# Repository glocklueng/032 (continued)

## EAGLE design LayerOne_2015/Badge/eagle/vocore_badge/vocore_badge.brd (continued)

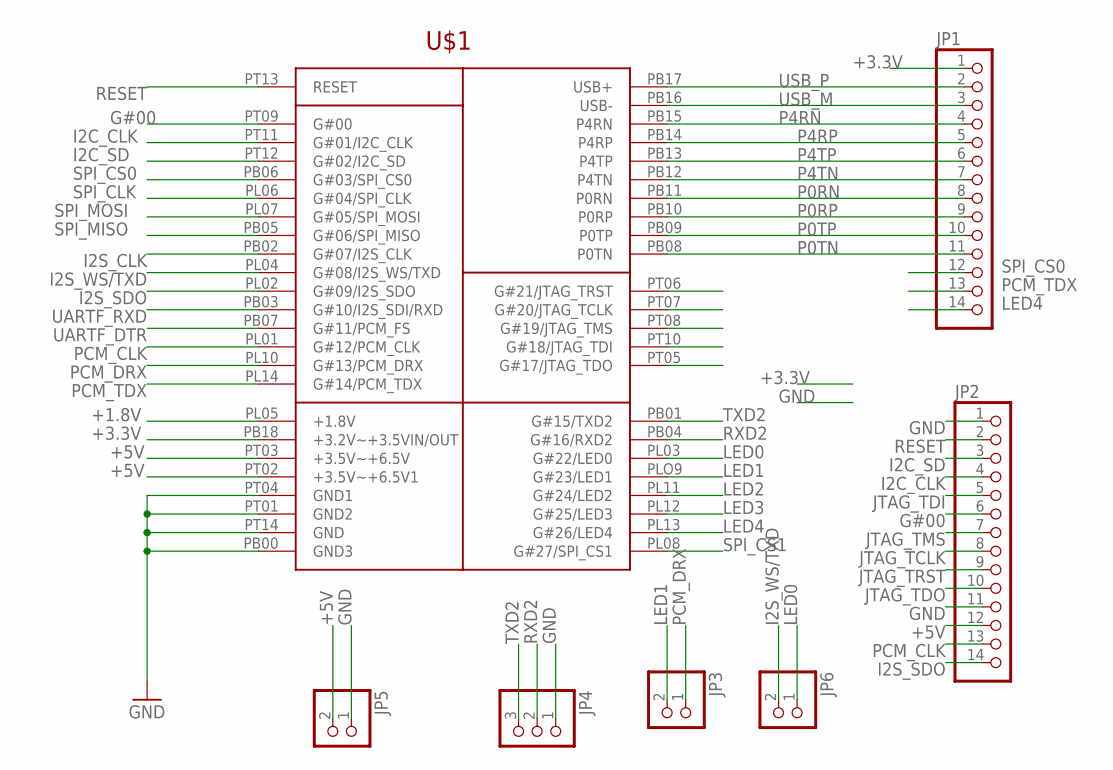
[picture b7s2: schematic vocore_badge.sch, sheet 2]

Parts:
JP1, JP2: PINHD-1X14; 1X14
JP3, JP5, JP6: PINHD-1X2; 1X02
JP4: PINHD-1X3; 1X03
U$1: VOCORE_SHIELD; VOCORE_DOC_CUSTOM

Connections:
+1.8V: U$1.PL05 (+1.8V); also elsewhere on the board
+3.3V: JP1.1, U$1.PB18 (+3.2V~+3.5VIN/OUT); also elsewhere on the board
+5V: JP2.12, JP5.2, U$1.PT02 (+3.5V~+6.5V1), U$1.PT03 (+3.5V~+6.5V); also elsewhere on the board
G#00: JP2.6, U$1.PT09 (G#00)
GND: JP2.1, JP2.11, JP4.1, JP5.1, U$1.PB00 (GND3), U$1.PT01 (GND2), U$1.PT04 (GND1), U$1.PT14 (GND); also elsewhere on the board
I2C_CLK: JP2.4, U$1.PT11 (G#01/I2C_CLK)
I2C_SD: JP2.3, U$1.PT12 (G#02/I2C_SD)
I2S_CLK: U$1.PB02 (G#07/I2S_CLK)
I2S_SDO: JP2.14, U$1.PL02 (G#09/I2S_SDO)
I2S_WS/TXD: JP6.2, U$1.PL04 (G#08/I2S_WS/TXD)
JTAG_TCLK: JP2.8, U$1.PT07 (G#20/JTAG_TCLK)
JTAG_TDI: JP2.5, U$1.PT10 (G#18/JTAG_TDI)
JTAG_TDO: JP2.10, U$1.PT05 (G#17/JTAG_TDO)
JTAG_TMS: JP2.7, U$1.PT08 (G#19/JTAG_TMS)
JTAG_TRST: JP2.9, U$1.PT06 (G#21/JTAG_TRST)
LED0: JP6.1, U$1.PL03 (G#22/LED0)
LED1: JP3.2, U$1.PLO9 (G#23/LED1)
LED2: U$1.PL11 (G#24/LED2); also elsewhere on the board
LED3: U$1.PL12 (G#25/LED3); also elsewhere on the board
LED4: JP1.14, U$1.PL13 (G#26/LED4)
P0RN: JP1.8, U$1.PB11 (P0RN); also elsewhere on the board
P0RP: JP1.9, U$1.PB10 (P0RP); also elsewhere on the board
P0TN: JP1.11, U$1.PB08 (P0TN); also elsewhere on the board
P0TP: JP1.10, U$1.PB09 (P0TP); also elsewhere on the board
P4RN: JP1.4, U$1.PB15 (P4RN); also elsewhere on the board
P4RP: JP1.5, U$1.PB14 (P4RP); also elsewhere on the board
P4TN: JP1.7, U$1.PB12 (P4TN); also elsewhere on the board
P4TP: JP1.6, U$1.PB13 (P4TP); also elsewhere on the board
PCM_CLK: JP2.13, U$1.PL01 (G#12/PCM_CLK)
PCM_DRX: JP3.1, U$1.PL10 (G#13/PCM_DRX)
PCM_TDX: JP1.13, U$1.PL14 (G#14/PCM_TDX)
RESET: JP2.2, U$1.PT13 (RESET)
RXD2: JP4.2, U$1.PB04 (G#16/RXD2); also elsewhere on the board
SPI_CLK: U$1.PL06 (G#04/SPI_CLK); also elsewhere on the board
SPI_CS0: JP1.12, U$1.PB06 (G#03/SPI_CS0)
SPI_CS1: U$1.PL08 (G#27/SPI_CS1); also elsewhere on the board
SPI_MISO: U$1.PB05 (G#06/SPI_MISO); also elsewhere on the board
SPI_MOSI: U$1.PL07 (G#05/SPI_MOSI); also elsewhere on the board
TXD2: JP4.3, U$1.PB01 (G#15/TXD2); also elsewhere on the board
UARTF_DTR: U$1.PB07 (G#11/PCM_FS); also elsewhere on the board
UARTF_RXD: U$1.PB03 (G#10/I2S_SDI/RXD); also elsewhere on the board
USB_M: JP1.3, U$1.PB16 (USB-); also elsewhere on the board
USB_P: JP1.2, U$1.PB17 (USB+); also elsewhere on the board

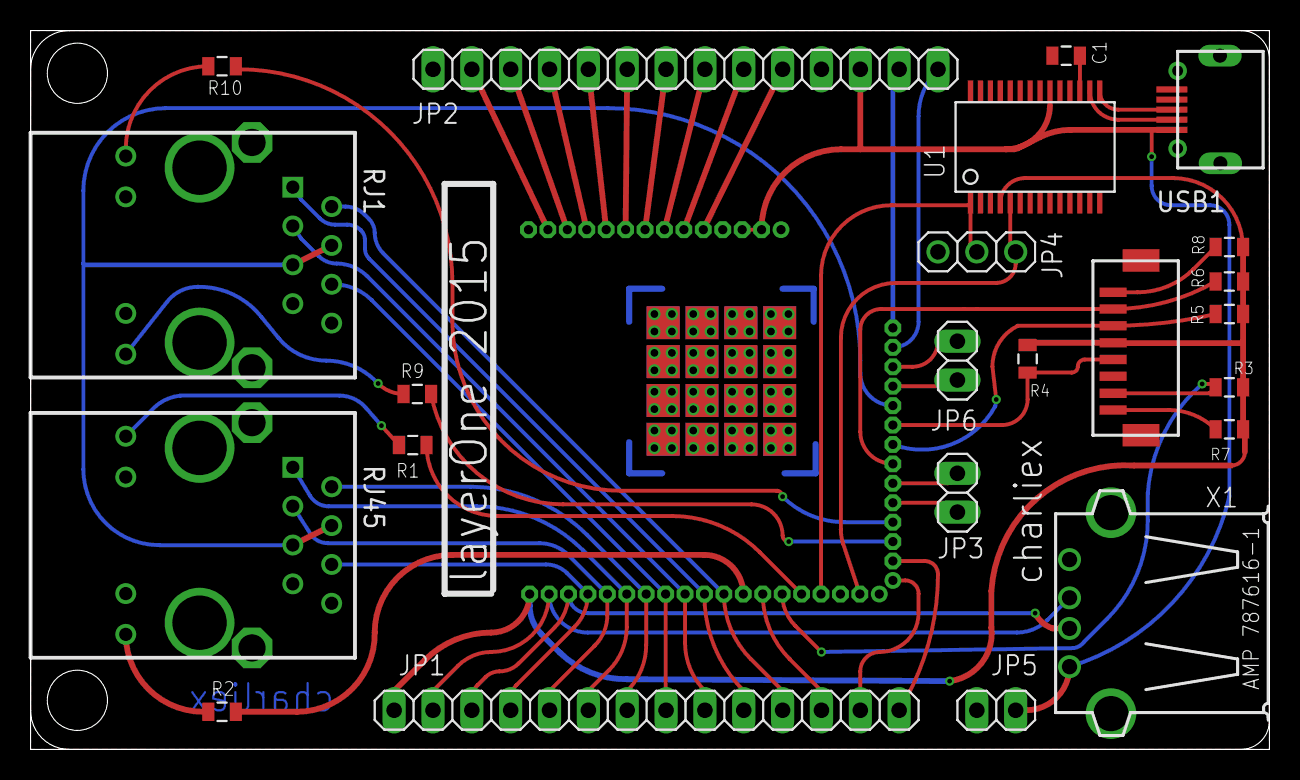
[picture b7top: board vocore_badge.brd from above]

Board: 2 copper layers, 81.0 x 47.0 mm, 24 parts (1 on the bottom side), 51 nets.

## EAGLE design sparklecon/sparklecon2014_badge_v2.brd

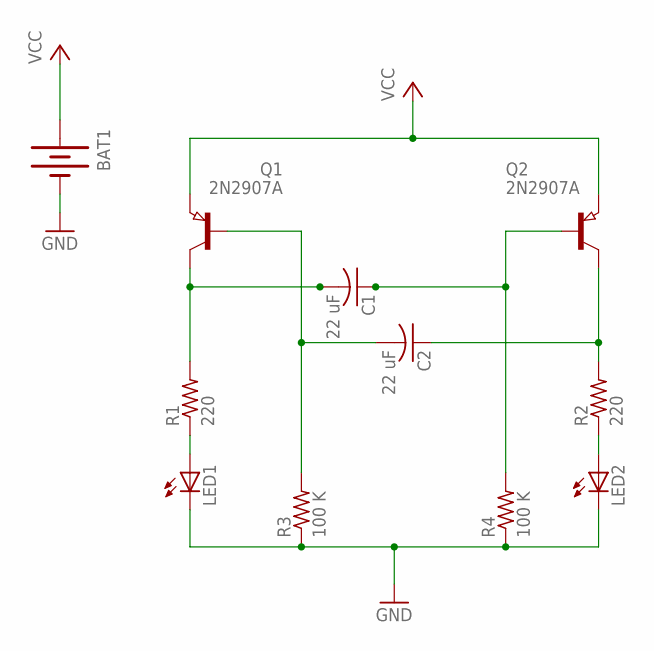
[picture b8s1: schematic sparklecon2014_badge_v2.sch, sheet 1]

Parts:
BAT1: BATTERY20PTH; BATTCOM_20MM_PTH
C1, C2: 22 uF; C1206K
LED1, LED2: LEDCHIPLED_1206; CHIPLED_1206
Q1, Q2: 2N2907A; SOT23
R1, R2: 220; R0805
R3, R4: 100 K; R0805

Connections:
GND: BAT1.2 (-), LED1.C, LED2.C, R3.1, R4.1; also elsewhere on the board
unnamed: C1.2, Q1.3 (C), R1.2
unnamed: C2.2, Q1.1 (B), R3.2
unnamed: LED2.A, R2.1
unnamed: LED1.A, R1.1
unnamed: C2.1, Q2.3 (C), R2.2
unnamed: C1.1, Q2.1 (B), R4.2
VCC: BAT1.1 (+), Q1.2 (E), Q2.2 (E)

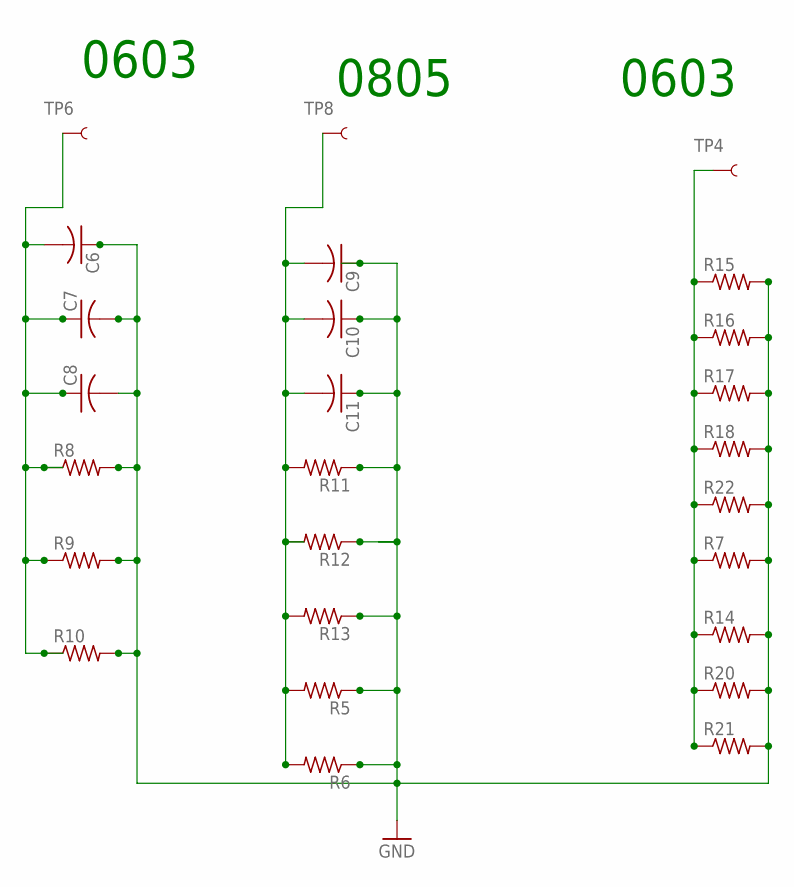
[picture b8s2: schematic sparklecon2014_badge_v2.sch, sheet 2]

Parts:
C6, C7, C8: C-USC1206; C1206
C9, C10, C11: C-USC0805; C0805
R5, R6, R11, R12, R13: R-US_R0805; R0805
R7, R14, R20, R21, R22: R-US_R0402; R0402
R8, R9, R10: R-US_R1206; R1206
R15, R16, R17, R18: R-US_R0603; R0603
TP4, TP6, TP8: TEST-POINT3X5; PAD.03X.05

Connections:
GND: C6.1, C7.2, C8.2, C9.1, C10.1, C11.1, R5.1, R6.1, R7.2, R8.2, R9.2, R10.2, R11.1, R12.1, R13.1, R14.2, R15.2, R16.2, R17.2, R18.2, R20.2, R21.2, R22.2; also elsewhere on the board
unnamed: R7.1, R14.1, R15.1, R16.1, R17.1, R18.1, R20.1, R21.1, R22.1, TP4.P$1
unnamed: C6.2, C7.1, C8.1, R8.1, R9.1, R10.1, TP6.P$1
unnamed: C9.2, C10.2, C11.2, R5.2, R6.2, R11.2, R12.2, R13.2, TP8.P$1

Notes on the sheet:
0603
0805

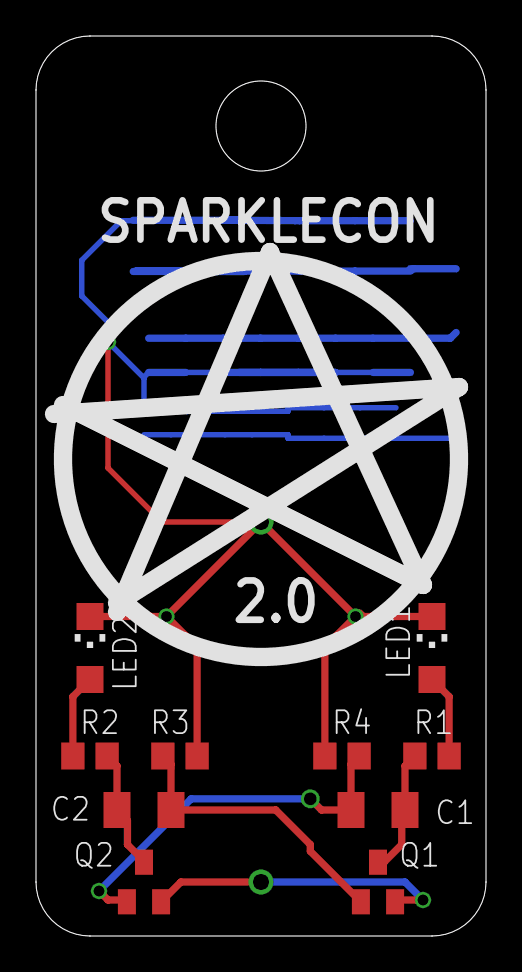
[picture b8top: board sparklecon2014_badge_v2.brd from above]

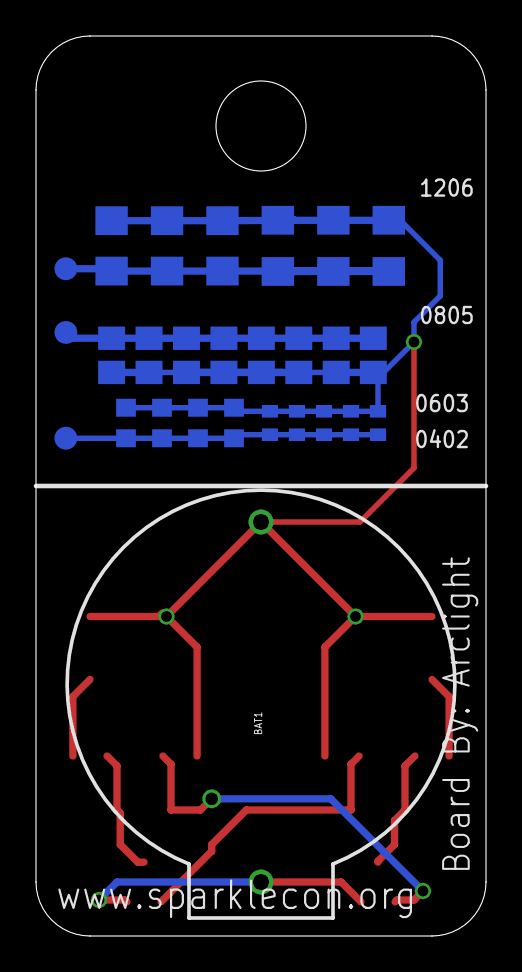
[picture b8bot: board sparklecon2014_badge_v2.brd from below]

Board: 2 copper layers, 25.0 x 50.0 mm, 37 parts (27 on the bottom side), 11 nets.

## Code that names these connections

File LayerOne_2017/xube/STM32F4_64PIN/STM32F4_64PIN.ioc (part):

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Mcu.Name=STM32F446R(C-E)Tx
Mcu.Package=LQFP64
Mcu.UserName=STM32F446RETx
PA10.GPIOParameters=GPIO_Label
PA10.GPIO_Label=USB_ID
PA10.Mode=OTG/Dual_Role_Device
PA10.Signal=USB_OTG_FS_ID
PA11.GPIOParameters=GPIO_Label
PA11.GPIO_Label=D-
PA11.Mode=OTG/Dual_Role_Device
PA11.Signal=USB_OTG_FS_DM
PA12.GPIOParameters=GPIO_Label
PA12.GPIO_Label=D+
PA12.Mode=OTG/Dual_Role_Device
PA12.Signal=USB_OTG_FS_DP
PA13.Mode=Serial_Wire
PA13.Signal=SYS_JTMS-SWDIO
PA14.Mode=Serial_Wire
PA14.Signal=SYS_JTCK-SWCLK
PA2.GPIOParameters=GPIO_Label
PA2.GPIO_Label=TFT_RESET
PA2.Signal=GPIO_Output
PA4.Signal=COMP_DAC1_group
PA5.GPIOParameters=GPIO_Label
PA5.GPIO_Label=TFT_SCK
PA5.Mode=Full_Duplex_Slave
PA5.Signal=SPI1_SCK
PA6.GPIOParameters=GPIO_Label
PA6.GPIO_Label=TFT_MISO
PA6.Mode=Full_Duplex_Slave
PA6.Signal=SPI1_MISO
PA7.GPIOParameters=GPIO_Label
PA7.GPIO_Label=TFT_MOSI
PA7.Mode=Full_Duplex_Slave
PA7.Signal=SPI1_MOSI
PA8.GPIOParameters=GPIO_Label
PA8.GPIO_Label=TFT_DC
PA8.Signal=GPIO_Output
PA9.Mode=Activate_VBUS
PA9.Signal=USB_OTG_FS_VBUS
PB10.GPIOParameters=GPIO_Label
PB10.GPIO_Label=SD_SCK
PB10.Mode=Full_Duplex_Master
PB10.Signal=SPI2_SCK
PB12.Mode=OTG/Dual-Role-Device-FS
PB12.Signal=USB_OTG_HS_ID
PB13.Mode=Activate_VBUS_FS
PB13.Signal=USB_OTG_HS_VBUS
PB14.Mode=OTG/Dual-Role-Device-FS
PB14.Signal=USB_OTG_HS_DM
PB15.Mode=OTG/Dual-Role-Device-FS
PB15.Signal=USB_OTG_HS_DP
PB5.Mode=Slave
PB5.Signal=CAN2_RX
PB6.Mode=Slave
PB6.Signal=CAN2_TX
PB8.Mode=Master
PB8.Signal=CAN1_RX
PB9.Mode=Master
PB9.Signal=CAN1_TX
PC1.GPIOParameters=GPIO_Label
PC1.GPIO_Label=SD_MOSI
PC1.Mode=Full_Duplex_Master
PC1.Signal=SPI2_MOSI
PC2.GPIOParameters=GPIO_Label
PC2.GPIO_Label=SD_MISO
PC2.Mode=Full_Duplex_Master
PC2.Signal=SPI2_MISO
PC7.GPIOParameters=GPIO_Label
PC7.GPIO_Label=TFT_CS
PC7.Signal=GPIO_Output
PC9.GPIOParameters=GPIO_Label
PC9.GPIO_Label=TFT_LCD
PC9.Signal=GPIO_Output
PH0-OSC_IN.Mode=HSE-External-Oscillator
PH0-OSC_IN.Signal=RCC_OSC_IN
PH1-OSC_OUT.Mode=HSE-External-Oscillator
PH1-OSC_OUT.Signal=RCC_OSC_OUT
RCC.SYSCLKFreq_VALUE=120000000
RCC.SYSCLKSource=RCC_SYSCLKSOURCE_PLLCLK
board=STM32F4_64PIN

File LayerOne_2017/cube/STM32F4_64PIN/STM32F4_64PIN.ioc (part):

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Mcu.Name=STM32F446R(C-E)Tx
Mcu.Package=LQFP64
Mcu.UserName=STM32F446RETx
PA11.GPIOParameters=GPIO_Speed,GPIO_PuPd,GPIO_Mode
PA11.GPIO_Mode=GPIO_MODE_AF_PP
PA11.GPIO_PuPd=GPIO_NOPULL
PA11.GPIO_Speed=GPIO_SPEED_FREQ_VERY_HIGH
PA11.Mode=Host_Only
PA11.Signal=USB_OTG_FS_DM
PA12.GPIOParameters=GPIO_Speed,GPIO_PuPd,GPIO_Mode
PA12.GPIO_Mode=GPIO_MODE_AF_PP
PA12.GPIO_PuPd=GPIO_NOPULL
PA12.GPIO_Speed=GPIO_SPEED_FREQ_VERY_HIGH
PA12.Mode=Host_Only
PA12.Signal=USB_OTG_FS_DP
PA13.Mode=Serial_Wire
PA13.Signal=SYS_JTMS-SWDIO
PA14.Mode=Serial_Wire
PA14.Signal=SYS_JTCK-SWCLK
PA4.Signal=COMP_DAC1_group
PA5.GPIOParameters=GPIO_Speed,GPIO_PuPd,GPIO_Mode
PA5.GPIO_Mode=GPIO_MODE_AF_PP
PA5.GPIO_PuPd=GPIO_NOPULL
PA5.GPIO_Speed=GPIO_SPEED_FREQ_VERY_HIGH
PA5.Mode=Full_Duplex_Slave
PA5.Signal=SPI1_SCK
PA6.GPIOParameters=GPIO_Speed,GPIO_PuPd,GPIO_Mode
PA6.GPIO_Mode=GPIO_MODE_AF_PP
PA6.GPIO_PuPd=GPIO_NOPULL
PA6.GPIO_Speed=GPIO_SPEED_FREQ_VERY_HIGH
PA6.Mode=Full_Duplex_Slave
PA6.Signal=SPI1_MISO
PA7.GPIOParameters=GPIO_Speed,GPIO_PuPd,GPIO_Mode
PA7.GPIO_Mode=GPIO_MODE_AF_PP
PA7.GPIO_PuPd=GPIO_NOPULL
PA7.GPIO_Speed=GPIO_SPEED_FREQ_VERY_HIGH
PA7.Mode=Full_Duplex_Slave
PA7.Signal=SPI1_MOSI
PA8.GPIOParameters=GPIO_Speed,PinState,GPIO_PuPd,GPIO_ModeDefaultOutputPP
PA8.GPIO_ModeDefaultOutputPP=GPIO_MODE_OUTPUT_PP
PA8.GPIO_PuPd=GPIO_NOPULL
PA8.GPIO_Speed=GPIO_SPEED_FREQ_LOW
PA8.PinState=GPIO_PIN_RESET
PA8.Signal=GPIO_Output
PA9.Mode=Activate_VBUS
PA9.Signal=USB_OTG_FS_VBUS
PB0.GPIOParameters=GPIO_PuPd,GPIO_Mode
PB0.GPIO_Mode=GPIO_MODE_INPUT
PB0.GPIO_PuPd=GPIO_NOPULL
PB0.Signal=GPIO_Input
PB1.GPIOParameters=GPIO_PuPd,GPIO_Mode
PB1.GPIO_Mode=GPIO_MODE_INPUT
PB1.GPIO_PuPd=GPIO_NOPULL
PB1.Signal=GPIO_Input
PB10.GPIOParameters=GPIO_Speed,GPIO_PuPd,GPIO_Mode
PB10.GPIO_Mode=GPIO_MODE_AF_PP
PB10.GPIO_PuPd=GPIO_NOPULL
PB10.GPIO_Speed=GPIO_SPEED_FREQ_VERY_HIGH
PB10.Mode=Full_Duplex_Master
PB10.Signal=SPI2_SCK
PB13.Mode=Activate_VBUS_FS
PB13.Signal=USB_OTG_HS_VBUS
PB14.Mode=Device_Only_FS
PB14.Signal=USB_OTG_HS_DM
PB15.Mode=Device_Only_FS
PB15.Signal=USB_OTG_HS_DP
PB2.GPIOParameters=GPIO_Speed,PinState,GPIO_PuPd,GPIO_ModeDefaultOutputPP
PB2.GPIO_ModeDefaultOutputPP=GPIO_MODE_OUTPUT_PP
PB2.GPIO_PuPd=GPIO_NOPULL
PB2.GPIO_Speed=GPIO_SPEED_FREQ_LOW
PB2.PinState=GPIO_PIN_RESET
PB2.Signal=GPIO_Output
PB5.Mode=Slave
PB5.Signal=CAN2_RX
PB6.Mode=Slave
PB6.Signal=CAN2_TX
PB8.Mode=Master
PB8.Signal=CAN1_RX
PB9.Mode=Master
PB9.Signal=CAN1_TX
PC1.GPIOParameters=GPIO_Speed,GPIO_PuPd,GPIO_Mode
PC1.GPIO_Mode=GPIO_MODE_AF_PP
PC1.GPIO_PuPd=GPIO_NOPULL
PC1.GPIO_Speed=GPIO_SPEED_FREQ_VERY_HIGH
PC1.Mode=Full_Duplex_Master
PC1.Signal=SPI2_MOSI
PC2.GPIOParameters=GPIO_Speed,GPIO_PuPd,GPIO_Mode
PC2.GPIO_Mode=GPIO_MODE_AF_PP
PC2.GPIO_PuPd=GPIO_NOPULL
PC2.GPIO_Speed=GPIO_SPEED_FREQ_VERY_HIGH
PC2.Mode=Full_Duplex_Master
PC2.Signal=SPI2_MISO
PC7.GPIOParameters=GPIO_Speed,PinState,GPIO_PuPd,GPIO_ModeDefaultOutputPP
PC7.GPIO_ModeDefaultOutputPP=GPIO_MODE_OUTPUT_PP
PC7.GPIO_PuPd=GPIO_NOPULL
PC7.GPIO_Speed=GPIO_SPEED_FREQ_LOW
PC7.PinState=GPIO_PIN_RESET
PC7.Signal=GPIO_Output
PC8.GPIOParameters=GPIO_Speed,PinState,GPIO_PuPd,GPIO_ModeDefaultOutputPP
PC8.GPIO_ModeDefaultOutputPP=GPIO_MODE_OUTPUT_PP
PC8.GPIO_PuPd=GPIO_NOPULL
PC8.GPIO_Speed=GPIO_SPEED_FREQ_LOW
PC8.PinState=GPIO_PIN_RESET
PC8.Signal=GPIO_Output
PC9.GPIOParameters=GPIO_Speed,PinState,GPIO_PuPd,GPIO_ModeDefaultOutputPP
PC9.GPIO_ModeDefaultOutputPP=GPIO_MODE_OUTPUT_PP
PC9.GPIO_PuPd=GPIO_NOPULL
PC9.GPIO_Speed=GPIO_SPEED_FREQ_LOW
PC9.PinState=GPIO_PIN_RESET
PC9.Signal=GPIO_Output
PH0-OSC_IN.Mode=HSE-External-Oscillator
PH0-OSC_IN.Signal=RCC_OSC_IN
PH1-OSC_OUT.Mode=HSE-External-Oscillator
PH1-OSC_OUT.Signal=RCC_OSC_OUT
RCC.HSE_Timout=1000
RCC.HSE_VALUE=8000000
RCC.SYSCLKFreq_VALUE=67200000
RCC.SYSCLKSource=RCC_SYSCLKSOURCE_PLLRCLK
board=STM32F4_64PIN

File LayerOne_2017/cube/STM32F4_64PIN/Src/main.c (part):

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  __HAL_RCC_GPIOB_CLK_ENABLE();
  __HAL_RCC_GPIOD_CLK_ENABLE();

  /*Configure GPIO pins : PC13 PC14 PC15 PC0 
                           PC3 PC4 PC5 PC6 
                           PC10 PC11 PC12 */
  GPIO_InitStruct.Pin = GPIO_PIN_13|GPIO_PIN_14|GPIO_PIN_15|GPIO_PIN_0 
                          |GPIO_PIN_3|GPIO_PIN_4|GPIO_PIN_5|GPIO_PIN_6 
                          |GPIO_PIN_10|GPIO_PIN_11|GPIO_PIN_12;
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  GPIO_InitStruct.Pull = GPIO_NOPULL;
  HAL_GPIO_Init(GPIOC, &GPIO_InitStruct);

  /*Configure GPIO pins : PA0 PA1 PA2 PA3 
                           PA10 PA15 */
  GPIO_InitStruct.Pin = GPIO_PIN_0|GPIO_PIN_1|GPIO_PIN_2|GPIO_PIN_3 
                          |GPIO_PIN_10|GPIO_PIN_15;
  GPIO_InitStruct.Mode = GPIO_MODE_ANALOG;
  GPIO_InitStruct.Pull = GPIO_NOPULL;
  HAL_GPIO_Init(GPIOA, &GPIO_InitStruct);

  /*Configure GPIO pins : PB0 PB1 */
  GPIO_InitStruct.Pin = GPIO_PIN_0|GPIO_PIN_1;
  GPIO_InitStruct.Mode = GPIO_MODE_INPUT;
  GPIO_InitStruct.Pull = GPIO_NOPULL;
  HAL_GPIO_Init(GPIOB, &GPIO_InitStruct);

  /*Configure GPIO pin : PB2 */
  GPIO_InitStruct.Pin = GPIO_PIN_2;
  GPIO_InitStruct.Mode = GPIO_MODE_OUTPUT_PP;
  GPIO_InitStruct.Pull = GPIO_NOPULL;
  GPIO_InitStruct.Speed = GPIO_SPEED_FREQ_LOW;
  HAL_GPIO_Init(GPIOB, &GPIO_InitStruct);

  /*Configure GPIO pins : PB12 PB3 PB4 PB7 */
  GPIO_InitStruct.Pin = GPIO_PIN_12|GPIO_PIN_3|GPIO_PIN_4|GPIO_PIN_7;
  GPIO_InitStruct.Mode = GPIO_MODE_ANALOG;
  GPIO_InitStruct.Pull = GPIO_NOPULL;
  HAL_GPIO_Init(GPIOB, &GPIO_InitStruct);

  /*Configure GPIO pins : PC7 PC8 PC9 */
  GPIO_InitStruct.Pin = GPIO_PIN_7|GPIO_PIN_8|GPIO_PIN_9;
  GPIO_InitStruct.Mode = GPIO_MODE_OUTPUT_PP;
  GPIO_InitStruct.Pull = GPIO_NOPULL;
  GPIO_InitStruct.Speed = GPIO_SPEED_FREQ_LOW;
  HAL_GPIO_Init(GPIOC, &GPIO_InitStruct);

  /*Configure GPIO pin : PA8 */
  GPIO_InitStruct.Pin = GPIO_PIN_8;
  GPIO_InitStruct.Mode = GPIO_MODE_OUTPUT_PP;
  GPIO_InitStruct.Pull = GPIO_NOPULL;
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
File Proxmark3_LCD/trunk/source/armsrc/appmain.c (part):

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{
  mode = mode ;
  
	// PA5  -> SPI_NCS3 chip select (spare)
	// PA9  -> SPI_NCS1 chip select (microSD)
	// PA10 -> SPI_NCS2 chip select (LCD)
	// PA11 -> SPI_NCS0 chip select (FPGA)
	// PA12 -> SPI_MISO Master-In Slave-Out
	// PA13 -> SPI_MOSI Master-Out Slave-In
	// PA14 -> SPI_SPCK Serial Clock

	// Disable PIO control of the following pins, allows use by the SPI peripheral
	AT91C_BASE_PIOA->PIO_PDR =
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

			AT91C_BASE_SPI->SPI_MR =
				(11 << 16)			|	// Peripheral Chip Select (selects LCD SPI_NCS2 or PA10)
				AT91C_SPI_MODFDIS	|	// Mode Fault Detection disabled
				AT91C_SPI_MSTR;			// Master Mode
				AT91C_BASE_SPI->SPI_CSR[2] =
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
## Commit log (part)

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2014-07-04 wrong place
2014-07-04 Added Craft code
2014-07-06 added LED and Button
2014-07-06 added NC jumper to AVcc pin
2014-07-12 changed switches and moved stuff for soldering ease
2014-07-12 Moved charging LEDs
2014-07-13 Rolled back to may 27th
2014-07-24 drill size.
2014-07-30 Added proper hex file and python that generate intel hex
2014-07-30 moved aux button
2014-08-02 Moved audio jack forward for clearance.
2014-08-02 -Added Craft demo project for Atmel Studio -Added new Sandbox (empty projects that compile for L1 Demoscene board) -> C & asm version
2014-08-03 Basic Blink Demo
2014-08-04 corrected parts #
2014-08-04 Updated VGA connector to the ones we have in stock
2014-08-05 -Added basic blink program example -Added basic saw wave sound example
2014-09-07 Added V3 of the Demoscene board (PIC Processor)
2014-09-07 Added ground vias near the DAC's
2014-09-10 Added Crystal and removed USBID switch
2014-09-11 Small modifications
2014-09-13 -Set Pins 6,7,8 on the VGA connector to ground for color ground return -Added ground vias for better return paths -Added two extra pads for hackery
2014-09-13 First working code where the GFX core boots!
2014-09-15 Color bars are close, but too many and fuzzy.
2014-09-17 Successful 640x480 at 60Hz
2014-09-17 Stable 320x240, but test monitor may not support it! Must try on another monitor!
2014-09-18 First demo "Bad Rain". Screen size is 190x480 @ 60hz. However we use the first 190 vertical lines so we effectively get 190x190.
2014-09-18 Second demo "Rainbow Vomit Rain" Screen size is 190x480 @ 60hz. However we use the first 190 vertical lines so we effectively get 190x190.
2014-09-22 190x190 @ 8bpp, color demo! VERY INEFFICIENT CODE, MUST RETURN TO FIX COMPILER OPT SETTINGS
2014-10-03 Filled screen with 320x480
2014-10-17 Updated with L1 logo and a few fonts are blown up
2014-10-18 Added V4 (PRODUCTION MODEL)
2014-11-17 started filling out docs etc
2014-11-17 moved to /Badge
2015-01-02 check prior to zener?
2015-01-02 isolation in polygons
2015-02-07 flipped layer 1 and 16
2015-02-07 adding lbr.
2015-02-08 restrings
2015-02-08 submitted gerbers
2015-02-08 flipped board back around 1<>16
2015-02-08 schematic/brd are in sync. gnd's are missing. some holes wrong size.
2015-02-09 added gnd's, smaller holes on ethernet jack
2015-02-09 accidently routed a trace over some pins when cleaning up very short airwires
2015-03-01 sides are correct
2015-03-02 initial checkin of vocore dock badge
2015-03-02 edited holes.
2015-04-13 elongated pads on 245 logic convertor
    fixed usb on badge
2015-04-14 added new footprint for 3v
2015-04-14 added had logo on 201 (move to silk layer!)
2015-04-14 added hackaday.com website name
2015-04-14 moved logo to silk layer.
2015-04-14 silk tidy, pre teardrop
2015-04-14 teardrops and power.
2015-04-15 moved led to eye
2015-04-15 whoops. crossing track fixed.
2015-04-15 more breakouts on dock
2015-04-16 moved battery holder hole
2015-04-16 version pushed to itead
2015-04-18 20k SDCARD
2015-04-18 logo start
2015-04-21 added reset of breakouts.
2015-04-21 ft232r vccio to 3.3v
2015-04-22 lengthened usb pads lengthened SD cards moved most resistors to layer 1 added cap to 3v3 for ftdi 232
2015-04-25 working on final layouts.
2015-05-24 57600 default wifi esp8266 speed.
2016-05-15 fixed bootloader path
2016-10-22 usb changes
2016-10-23 revised submission to itead
2016-10-23 added reset switch
2016-10-30 fixed timing bugs, added mode list.
2016-11-04 cpu updated.
2016-11-04 updates to smaller lqfp64 board.
2016-11-04 prepping for release to factory
2016-11-05 supercon
2016-11-05 second pcb
2016-11-13 capactirors
2016-11-20 removed led resistors. fixed gnds
2016-11-20 renamed parts of 5v to add boost converter
2016-11-22 Added On/Off and UVLO
2016-11-24 Ugly but routed. except for 3 lines on page 8 to MCU not connected
2016-11-24 no silk screen in power section
2016-11-24 corners rounded
2016-11-25 Add voltage divider at Temp Sense of battery incase we need wider range in charge temp
2016-11-26 Backlight NPN redone
2016-11-26 Added Power test points
2016-11-27 third rev
2016-12-12 fixed usb moved reset button.
2016-12-18 working version, brings up usb as HID input device
2016-12-23 xmas update! added leds added caps to d+/d- fixed led backlight added cap to vreg
2016-12-23 fixed nrst via
2016-12-23 elongated cpu pads.
2016-12-24 basic working CDC, just echos back
2016-12-25 added tft test code. spi dma
2016-12-27 fourth rev
2016-12-28 started to clean up the layout a bit around the can bus added DNP resistors to pin 5 to support other SN65HVD23x variants
2016-12-29 updated to latest working code.
2017-01-15 support for 413/405 cpus as well
2017-01-26 working new board
